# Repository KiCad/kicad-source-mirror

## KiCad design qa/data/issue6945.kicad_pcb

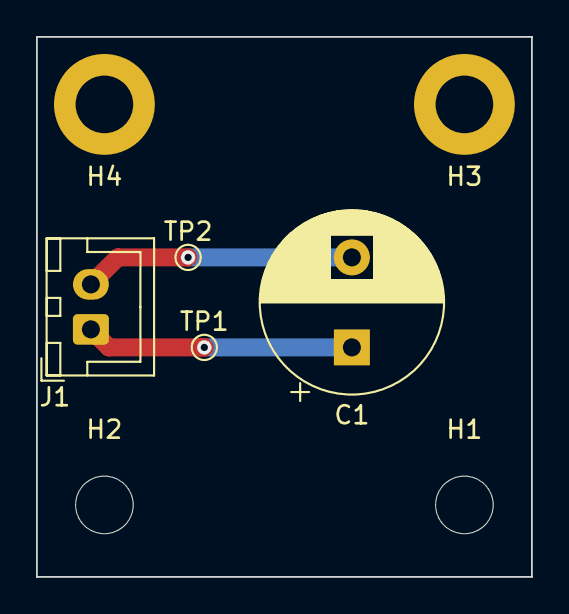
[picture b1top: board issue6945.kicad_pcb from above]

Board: 2 copper layers, 27.5 x 30.0 mm, 8 parts (0 on the bottom side), 2 nets.

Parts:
C1: 1m25vPY_5x10x16; CP_Radial_D10.0mm_P5.00mm
H1, H2: NPTH-3mm; MountingHole_3.2mm_M3
H3, H4: PTH-3mm; MountingHole_3.2mm_M3_DIN965_Pad
J1: XH-2A; JST_XH_B2B-XH-A_1x02_P2.50mm_Vertical
TP1, TP2: 1mm; TestPoint_Pad_D1.0mm

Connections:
GND: C1.2, J1.2, TP2.1
unnamed: C1.1, J1.1, TP1.1

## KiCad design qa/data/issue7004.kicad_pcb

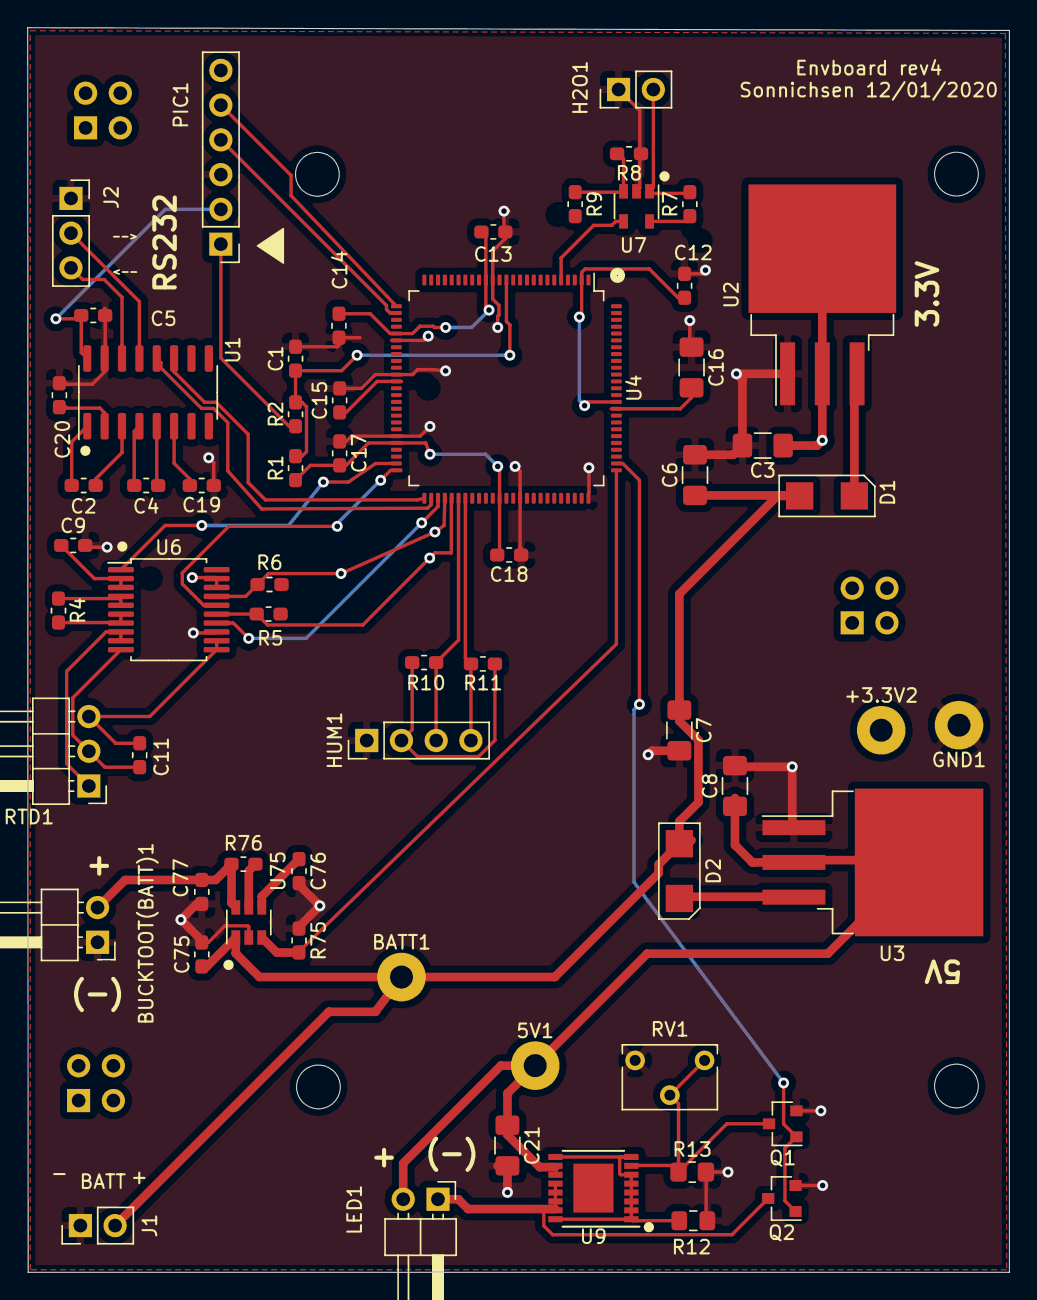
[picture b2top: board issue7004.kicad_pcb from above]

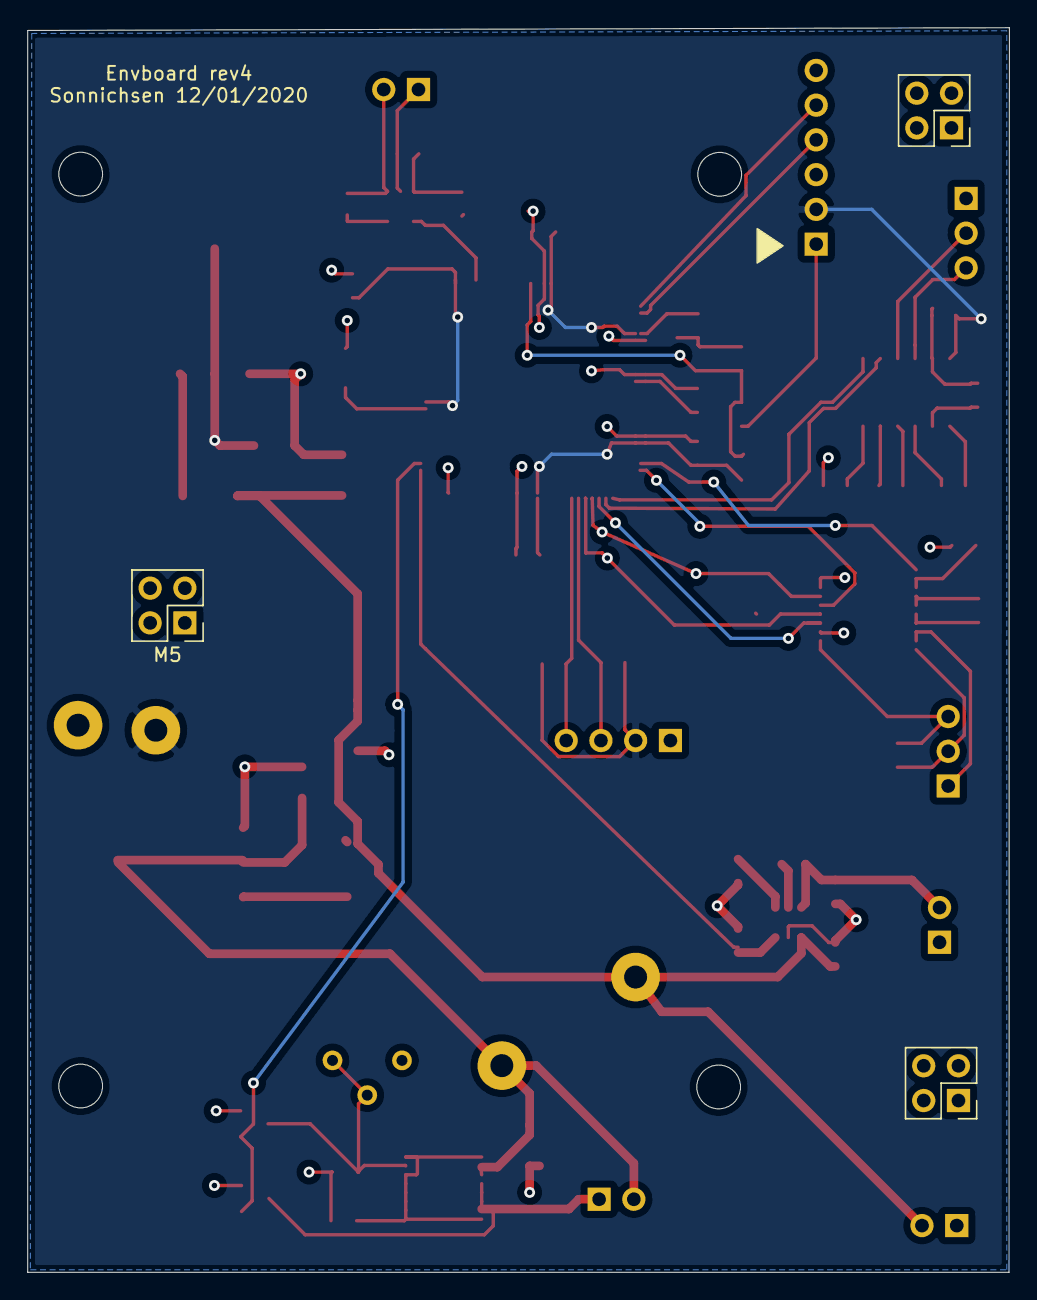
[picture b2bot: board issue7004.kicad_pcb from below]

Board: 2 copper layers, 71.8 x 91.0 mm, 69 parts (7 on the bottom side), 44 nets.

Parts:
5V1: TestPoint; post_small
+3.3V2: TestPoint; post_small
BATT1: TestPoint; post_small
BUCKTOOT(BATT)1: Conn_01x02; PinHeader_1x02_P2.54mm_Horizontal
C1, C2, C4, C5, C9, C11, C12, C13, C14, C15, C17, C18, C19, C20: 0.1uF; C_0603_1608Metric_Pad1.05x0.95mm_HandSolder
C3, C6, C7, C8, C16, C21: 10uF; C_1206_3216Metric_Pad1.42x1.75mm_HandSolder
C75: 1uF; R_0603_1608Metric_Pad1.05x0.95mm_HandSolder
C76: 0.01uF; R_0603_1608Metric_Pad1.05x0.95mm_HandSolder
C77: 0.1uF; R_0603_1608Metric_Pad1.05x0.95mm_HandSolder
D1, D2: MBRA130; 403D
GND1: TestPoint; post_small
H2O1: Conn_01x02; PinHeader_1x02_P2.54mm_Vertical
HUM1: SPARKSi7021; PinHeader_1x04_P2.54mm_Vertical
J1: Conn_01x02; PinHeader_1x02_P2.54mm_Vertical
J2: Conn_01x03; PinSocket_1x03_P2.54mm_Vertical
LED1: Conn_01x02; PinHeader_1x02_P2.54mm_Horizontal
M1, M2, M5: Conn_02x02_Odd_Even; PinHeader_2x02_P2.54mm_Vertical
PIC1: Conn_01x06; PinHeader_1x06_P2.54mm_Vertical
Q1, Q2: DMG3406L; SOT-23
R1, R5, R6, R10, R11, R75, R76: 10K; R_0603_1608Metric_Pad1.05x0.95mm_HandSolder
R2: 470; R_0603_1608Metric_Pad1.05x0.95mm_HandSolder
R4: 4K; R_0603_1608Metric_Pad1.05x0.95mm_HandSolder
R7: 1M; R_0603_1608Metric_Pad1.05x0.95mm_HandSolder
R8, R9: 100K; R_0603_1608Metric_Pad1.05x0.95mm_HandSolder
R12: 0.5ohms; R_0805_2012Metric_Pad1.15x1.40mm_HandSolder
R13: 15K; R_0805_2012Metric_Pad1.20x1.40mm_HandSolder
RTD1: Conn_01x03; PinHeader_1x03_P2.54mm_Horizontal
RV1: 50K; Potentiometer_Bourns_3266W_Vertical
U1: MAX3232CSE; SOIC-16_3.9x9.9mm_P1.27mm
U2: LM1084-3.3; TO-263-3_TabPin2
U3: LM1084-5.0; TO-263-3_TabPin2
U4: PIC24
U6: MAX31865xAP; MAX31865
U7: TL331; SOT-23-5
U9: LT3083; TSSOP-16-1EP_4.4x5mm_P0.65mm
U75: TPS22810; SOT-23-6
h1, h2, h3, h4: MountingHole_3.2mm_M3

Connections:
+3V3: +3.3V2.1, C3.1, C5.1, C9.1, C12.2, C13.2, C14.2, C15.2, C17.2, C18.2, HUM1.2, PIC1.2, R1.1, R5.2, R6.2, R7.1, R9.2, R10.2, R11.2, U1.16, U2.2, U4.2, U4.16, U4.30, U4.37, U4.46, U4.62, U4.86, U6.2, U6.3, U7.5
+5V: 5V1.1, C8.1, C21.1, LED1.2, U3.2, U9.10, U9.11
BATT: BATT1.1, C6.1, C7.1, C75.1, D1.2, D2.2, J1.2, U75.1
BUCK: R75.2, U4.76, U75.3
GND: BUCKTOOT(BATT)1.1, C1.2, C3.2, C5.2, C6.2, C7.2, C8.2, C9.2, C12.1, C13.1, C14.1, C15.1, C16.1, C17.1, C18.1, C19.1, C20.2, C21.2, C75.2, C76.2, C77.2, GND1.1, H2O1.1, HUM1.1, J1.1, J2.1, PIC1.3, Q1.2, Q2.2, R8.1, R12.2, R13.2, R75.1, RV1.3, U1.15, U2.1, U3.1, U4.15, U4.31, U4.36, U4.45, U4.65, U4.75, U6.13, U6.18, U6.19, U7.2, U75.2
H2O: U4.5, U7.4
LED: Q1.1, Q2.1, U4.77
MCLR: C1.1, R1.2, R2.2, U4.13
MISO: R6.1, U4.54, U6.17
MOSI: U4.53, U6.14
unnamed: BUCKTOOT(BATT)1.2, C77.1, R76.2, U75.6
unnamed: C2.1, U1.1
unnamed: C2.2, U1.3
unnamed: C4.1, U1.4
unnamed: C4.2, U1.5
unnamed: C11.1, RTD1.3, U6.11, U6.12
unnamed: C11.2, RTD1.2, U6.10
unnamed: C16.2, U4.85
unnamed: C19.2, U1.6
unnamed: C20.1, U1.2
unnamed: C76.1, U75.4
unnamed: D1.1, U2.3
unnamed: D2.1, U3.3
unnamed: H2O1.2, R7.2, U7.1
unnamed: J2.2, U1.13
unnamed: J2.3, U1.14
unnamed: LED1.1, Q2.3, U9.12, U9.13, U9.14, U9.15
unnamed: PIC1.1, R2.1
unnamed: Q1.3, R13.1, RV1.1, RV1.2, U9.7
unnamed: R4.1, U6.4, U6.5
unnamed: R4.2, U6.6, U6.7
unnamed: R8.2, R9.1, U7.3
unnamed: R12.1, U9.1, U9.2, U9.3, U9.4, U9.5, U9.6, U9.8, U9.9, U9.16
unnamed: R76.1, U75.5
unnamed: RTD1.1, U6.8, U6.9
PGC: PIC1.5, U4.26
PGD: PIC1.4, U4.27
PR5: U1.12, U4.52
PT5: U1.11, U4.51
SCK1: R5.1, U4.55, U6.15
SCL1: HUM1.4, R11.1, U4.57
SDA1: HUM1.3, R10.1, U4.56
\CS: U4.50, U6.16
\DRDY: U4.49, U6.1

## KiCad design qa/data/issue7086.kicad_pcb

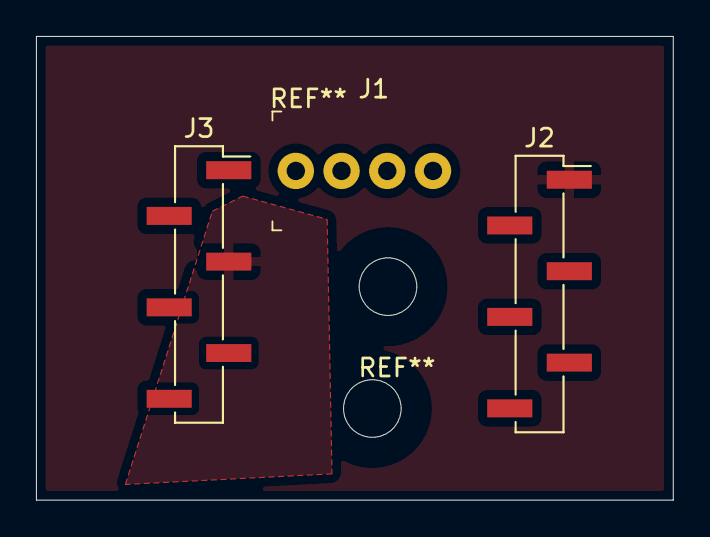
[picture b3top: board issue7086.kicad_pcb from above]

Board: 2 copper layers, 35.4 x 25.8 mm, 4 parts (0 on the bottom side), 2 nets, no tracks yet.

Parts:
H1: MountingHole; MountingHole_3.2mm_M3_DIN965
J1: 0022232041; PinHeader_1x4_P2.54mm_Drill1.02mm
J2, J3: 0022232041; PinHeader_1x06_P2.54mm_Vertical_SMD_Pin1Right

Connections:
unnamed: J1.2, J3.1
unnamed: J1.1, J1.4, J2.4, J3.4

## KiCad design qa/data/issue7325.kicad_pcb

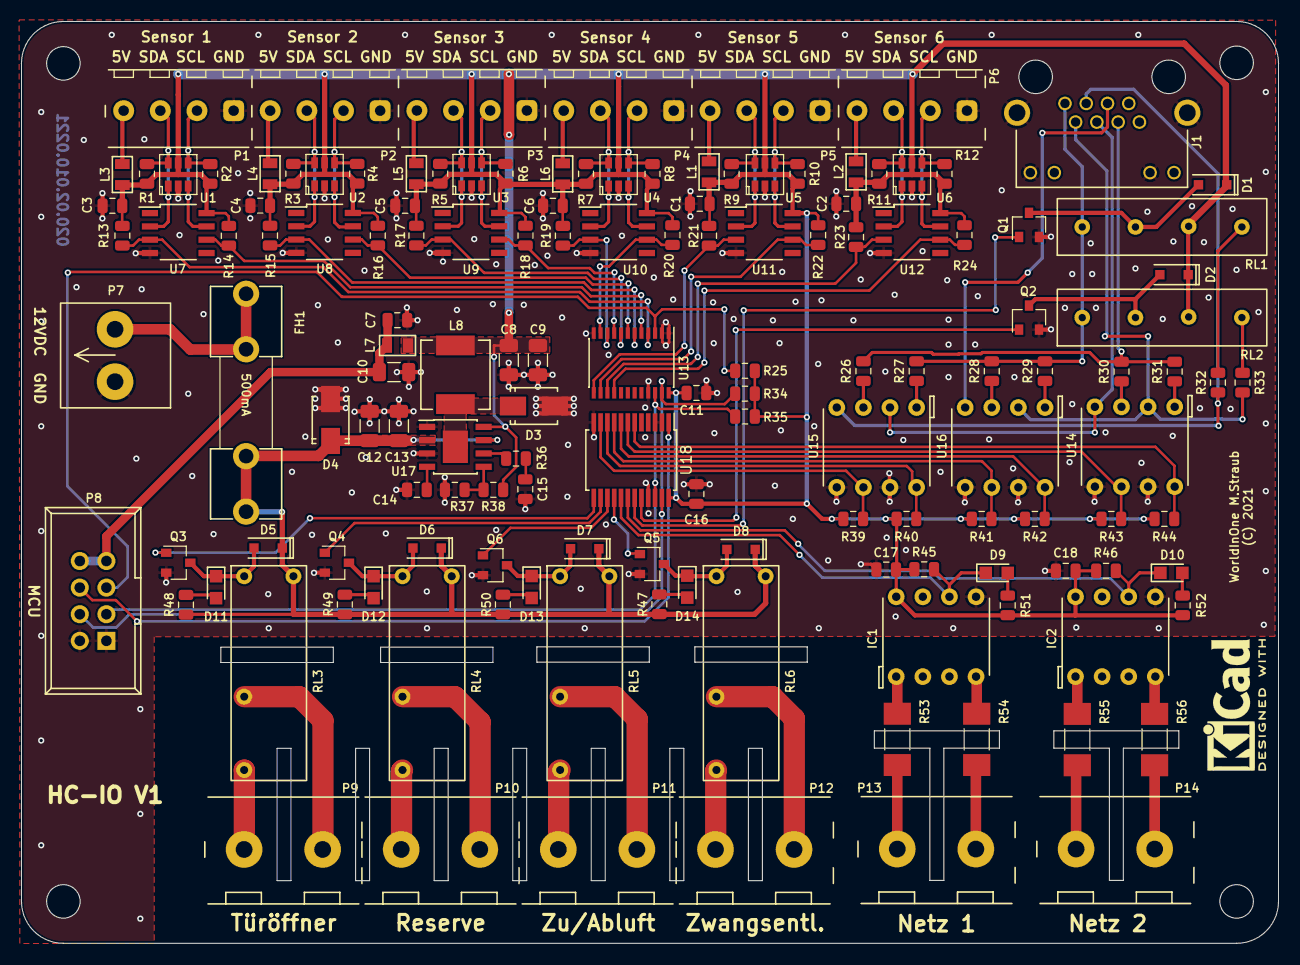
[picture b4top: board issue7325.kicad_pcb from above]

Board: 2 copper layers, 120.0 x 88.0 mm, 148 parts (0 on the bottom side), 100 nets.

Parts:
C1, C2, C3, C4, C5, C6: 1µ; C_0805_2012Metric_95
C7, C11, C14, C16, C17, C18: 100N; C_0805_2012Metric_60
C8, C9, C10, C12, C13: 22µ; C_1206_3216Metric_95
C15: 1.8N; C_0805_2012Metric_60
D1, D2, D5, D6, D7, D8: 1N4148WS; SOD-323
D3, D4: SS34; SMA_Standard
D9, D10: LED0805-Y; LED_0805
D11, D12, D13, D14: LED0805-G; LED_0805
FH1: FC5X20; Fuseholder5x20_horizontal_open_inline_1
IC1, IC2: HCPL-3760; DIP-8_W7.62mm_Socketed
J1: RJ45_LEDs_Shield
L1, L2, L3, L4, L5, L6, L7: FB; INDC2012X110
L8: 10µ; Inductor_0630
MH1, MH2, MH3, MH4: MHNP_M3; MountingHole_3.2mm_M3
P1, P2, P3, P4, P5, P6: KF128-4-3.5
P7: KF128-2-5.0
P8: IDCMV-4-2; IDC_Header_Straight_8pins
P9, P10, P11, P12, P13, P14: KF128-7.5-2; Terminal_Block_KF128_7.5mm-2pol
Q1, Q2, Q3, Q4, Q5, Q6: BSS138; SOT-23
R1, R2, R3, R4, R5, R6, R7, R8, R9, R10, R11, R12: 680E; R_0805_2012Metric
R13, R14, R15, R16, R17, R18, R19, R20, R21, R22, R23, R24, R25, R34, R35: 2.2K; R_0805_2012Metric
R26, R27, R28, R29, R30: 150E; R_0805_2012Metric
R31: 560E; R_0805_2012Metric
R32, R33: 10K; R_0805_2012Metric
R36: 27K; R_0805_2012Metric
R37: 9.53K; R_0805_2012Metric
R38: 49.9K; R_0805_2012Metric
R39, R40, R41, R42, R43, R44: 1K; R_0805_2012Metric
R45, R46, R51, R52: 4.7K; R_0805_2012Metric
R47, R48, R49, R50: 3.3K; R_0805_2012Metric
R53, R54, R55, R56: 82K; R_MELF_MMB-0207
RL1, RL2: SIP-1A5
RL3, RL4, RL5, RL6: G5NB-5; Relais_G5NB
U1, U2, U3, U4, U5, U6: USBLC6-2SC6; SOT-23-6
U7, U8, U9, U10, U11, U12: P82B715; SOIC-8_3.9x4.9mm_Pitch1.27mm
U13: PCA9548A; TSSOP-24_4.4x7.8mm_Pitch0.65mm
U14, U15, U16: LTV-827C; DIP-8_W7.62mm_Socketed
U17: AOZ3015; SOIC-8-1EP_3.9x4.9mm_Pitch1.27mm_PowerPAD
U18: PCF8575; SSOP-24_5.3x8.2mm_Pitch0.65mm

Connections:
/5V: C1.1, C2.1, C3.1, C4.1, C5.1, C6.1, C8.1, C9.1, C11.1, C16.2, C17.2, C18.2, D1.1 (K), D2.1 (K), IC1.8 (VCC), IC2.8 (VCC), L1.1, L2.1, L3.1, L4.1, L5.1, L6.1, L7.1, L8.2, R1.1, R2.2, R3.1, R4.2, R5.1, R6.2, R7.1, R8.2, R9.1, R10.2, R11.1, R12.2, R13.1, R14.1, R15.1, R16.1, R17.1, R18.1, R19.1, R20.1, R21.1, R22.1, R23.1, R24.1, R25.2, R34.1, R35.1, R38.2, R39.1, R40.1, R41.1, R42.1, R43.1, R44.1, R45.1, R46.1, R51.1, R52.1, RL1.3, RL2.3, U1.5 (VBUS), U2.5 (VBUS), U3.5 (VBUS), U4.5 (VBUS), U5.5 (VBUS), U6.5 (VBUS), U7.8 (Vcc), U8.8 (Vcc), U9.8 (Vcc), U10.8 (Vcc), U11.8 (Vcc), U12.8 (Vcc), U13.24 (VCC), U17.8 (VOUT), U18.24 (VDD)
/5VMCU: C7.1, C10.1, L7.2, P8.7, P8.8
/12V: C12.1, C13.1, D4.1 (K), D5.1 (K), D6.1 (K), D7.1 (K), D8.1 (K), FH1.2, R47.2, R48.2, R49.2, R50.2, RL3.4, RL4.4, RL5.4, RL6.4, U17.2 (VIN), U17.7 (EN)
/230V & general interface/230V1: D9.1 (K), IC1.6 (Vo), R45.2, U18.17 (IO1_4)
/230V & general interface/230V2: D10.1 (K), IC2.6 (Vo), R46.2, U18.18 (IO1_5)
/230V & general interface/AUX: Q4.1 (G), U18.14 (IO1_1)
/230V & general interface/BTL1: R42.2, U16.8, U18.8 (IO0_4)
/230V & general interface/BTL3: R40.2, U15.8, U18.10 (IO0_6)
/230V & general interface/BTL4: R41.2, U16.6, U18.9 (IO0_5)
/230V & general interface/BTL5: R44.2, U14.8, U18.6 (IO0_2)
/230V & general interface/BTL6: R39.2, U15.6, U18.11 (IO0_7)
/230V & general interface/BTL7: R43.2, U14.6, U18.7 (IO0_3)
/230V & general interface/BTP1: J1.1, R27.2, R28.2, R29.2, RL1.1, RL2.1
/230V & general interface/BTP2: J1.2, R33.2, U14.2, U16.2
/230V & general interface/BTP3: J1.3, R32.2, U15.4
/230V & general interface/BTP4: J1.4, U14.4, U15.2
/230V & general interface/BTP5: J1.5, U16.4
/230V & general interface/BTP6: J1.6, R26.2, R30.2, R31.2
/230V & general interface/DOOR: Q3.1 (G), U18.13 (IO1_0)
/230V & general interface/ENTFON: Q2.1 (G), U18.20 (IO1_7)
/230V & general interface/ENTFRH: Q1.1 (G), U18.19 (IO1_6)
/230V & general interface/ZUAB: Q6.1 (G), U18.15 (IO1_2)
/230V & general interface/ZWANG: Q5.1 (G), U18.16 (IO1_3)
/AM2315 sensors I2C interface/S0SCL: P1.2, R2.1, U1.3 (IO2), U1.4 (IO2), U7.7 (Ly)
/AM2315 sensors I2C interface/S0SDA: P1.3, R1.2, U1.1 (IO1), U1.6 (IO1), U7.2 (Lx)
/AM2315 sensors I2C interface/S1SCL: P2.2, R4.1, U2.3 (IO2), U2.4 (IO2), U8.7 (Ly)
/AM2315 sensors I2C interface/S1SDA: P2.3, R3.2, U2.1 (IO1), U2.6 (IO1), U8.2 (Lx)
/AM2315 sensors I2C interface/S2SCL: P3.2, R6.1, U3.3 (IO2), U3.4 (IO2), U9.7 (Ly)
/AM2315 sensors I2C interface/S2SDA: P3.3, R5.2, U3.1 (IO1), U3.6 (IO1), U9.2 (Lx)
/AM2315 sensors I2C interface/S3SCL: P4.2, R8.1, U4.3 (IO2), U4.4 (IO2), U10.7 (Ly)
/AM2315 sensors I2C interface/S3SDA: P4.3, R7.2, U4.1 (IO1), U4.6 (IO1), U10.2 (Lx)
/AM2315 sensors I2C interface/S4SCL: P5.2, R10.1, U5.3 (IO2), U5.4 (IO2), U11.7 (Ly)
/AM2315 sensors I2C interface/S4SDA: P5.3, R9.2, U5.1 (IO1), U5.6 (IO1), U11.2 (Lx)
/AM2315 sensors I2C interface/S5SCL: P6.2, R12.1, U6.3 (IO2), U6.4 (IO2), U12.7 (Ly)
/AM2315 sensors I2C interface/S5SDA: P6.3, R11.2, U6.1 (IO1), U6.6 (IO1), U12.2 (Lx)
/NIOINT: P8.6, U18.1 (~INT)
/NIORESET: P8.5, R25.1, U13.3 (~RESET)
/SCL: P8.3, R35.2, U13.22 (SCL), U18.22 (SCL)
/SDA: P8.4, R34.2, U13.23 (SDA), U18.23 (SDA)
GND: C1.2, C2.2, C3.2, C4.2, C5.2, C6.2, C7.2, C8.2, C9.2, C10.2, C11.2, C12.2, C13.2, C14.2, C15.2, C16.1, C17.1, C18.1, D3.2 (A), D4.2 (A), IC1.5 (GND), IC2.5 (GND), J1.GK, J1.Shld (Shield), J1.YK, P1.1, P2.1, P3.1, P4.1, P5.1, P6.1, P7.1, P8.1, P8.2, Q1.2 (S), Q2.2 (S), Q3.2 (S), Q4.2 (S), Q5.2 (S), Q6.2 (S), R37.1, U1.2 (GND), U2.2 (GND), U3.2 (GND), U4.2 (GND), U5.2 (GND), U6.2 (GND), U7.4 (GND), U8.4 (GND), U9.4 (GND), U10.4 (GND), U11.4 (GND), U12.4 (GND), U13.1 (A0), U13.2 (A1), U13.12 (GND), U13.21 (A2), U14.5, U14.7, U15.5, U15.7, U16.5, U16.7, U17.1 (PGND), U17.3 (AGND), U18.2 (A1), U18.3 (A2), U18.12 (VSS), U18.21 (A0)
unnamed: C14.1, U17.4 (VCC)
unnamed: C15.1, R36.1
unnamed: D1.2 (A), Q1.3 (D), RL1.2
unnamed: D2.2 (A), Q2.3 (D), RL2.2
unnamed: D3.1 (K), L8.1, U17.9 (LX)
unnamed: D9.2 (A), R51.2
unnamed: D10.2 (A), R52.2
unnamed: D5.2 (A), D11.1 (K), Q3.3 (D), RL3.1
unnamed: D11.2 (A), R48.1
unnamed: D6.2 (A), D12.1 (K), Q4.3 (D), RL4.1
unnamed: D12.2 (A), R49.1
unnamed: D7.2 (A), D13.1 (K), Q6.3 (D), RL5.1
unnamed: D13.2 (A), R50.1
unnamed: D8.2 (A), D14.1 (K), Q5.3 (D), RL6.1
unnamed: D14.2 (A), R47.1
unnamed: FH1.1, P7.2
unnamed: IC1.1 (AC+), R53.1
unnamed: IC1.4 (AC-), R54.1
unnamed: IC2.1 (AC+), R55.1
unnamed: IC2.4 (AC-), R56.1
unnamed: L1.2, P5.4
unnamed: L2.2, P6.4
unnamed: L3.2, P1.4
unnamed: L4.2, P2.4
unnamed: L5.2, P3.4
unnamed: L6.2, P4.4
unnamed: P9.1, RL3.2
unnamed: P9.2, RL3.3
unnamed: P10.1, RL4.2
unnamed: P10.2, RL4.3
unnamed: P11.1, RL5.2
unnamed: P11.2, RL5.3
unnamed: P12.1, RL6.2
unnamed: P12.2, RL6.3
unnamed: P13.1, R54.2
unnamed: P13.2, R53.2
unnamed: P14.1, R56.2
unnamed: P14.2, R55.2
unnamed: R13.2, U7.3 (Sx), U13.4 (SD0)
unnamed: R14.2, U7.6 (Sy), U13.5 (SC0)
unnamed: R15.2, U8.3 (Sx), U13.6 (SD1)
unnamed: R16.2, U8.6 (Sy), U13.7 (SC1)
unnamed: R17.2, U9.3 (Sx), U13.8 (SD2)
unnamed: R18.2, U9.6 (Sy), U13.9 (SC2)
unnamed: R19.2, U10.3 (Sx), U13.10 (SD3)
unnamed: R20.2, U10.6 (Sy), U13.11 (SC3)
unnamed: R21.2, U11.3 (Sx), U13.13 (SD4)
unnamed: R22.2, U11.6 (Sy), U13.14 (SC4)
unnamed: R23.2, U12.3 (Sx), U13.15 (SD5)
unnamed: R24.2, U12.6 (Sy), U13.16 (SC5)
unnamed: R26.1, U15.3
unnamed: R27.1, U15.1
unnamed: R28.1, U16.3
unnamed: R29.1, U16.1
unnamed: R30.1, U14.3
unnamed: R31.1, U14.1
unnamed: R32.1, RL1.4
unnamed: R33.1, RL2.4
unnamed: R36.2, U17.6 (CMP)
unnamed: R37.2, R38.1, U17.5 (FB)

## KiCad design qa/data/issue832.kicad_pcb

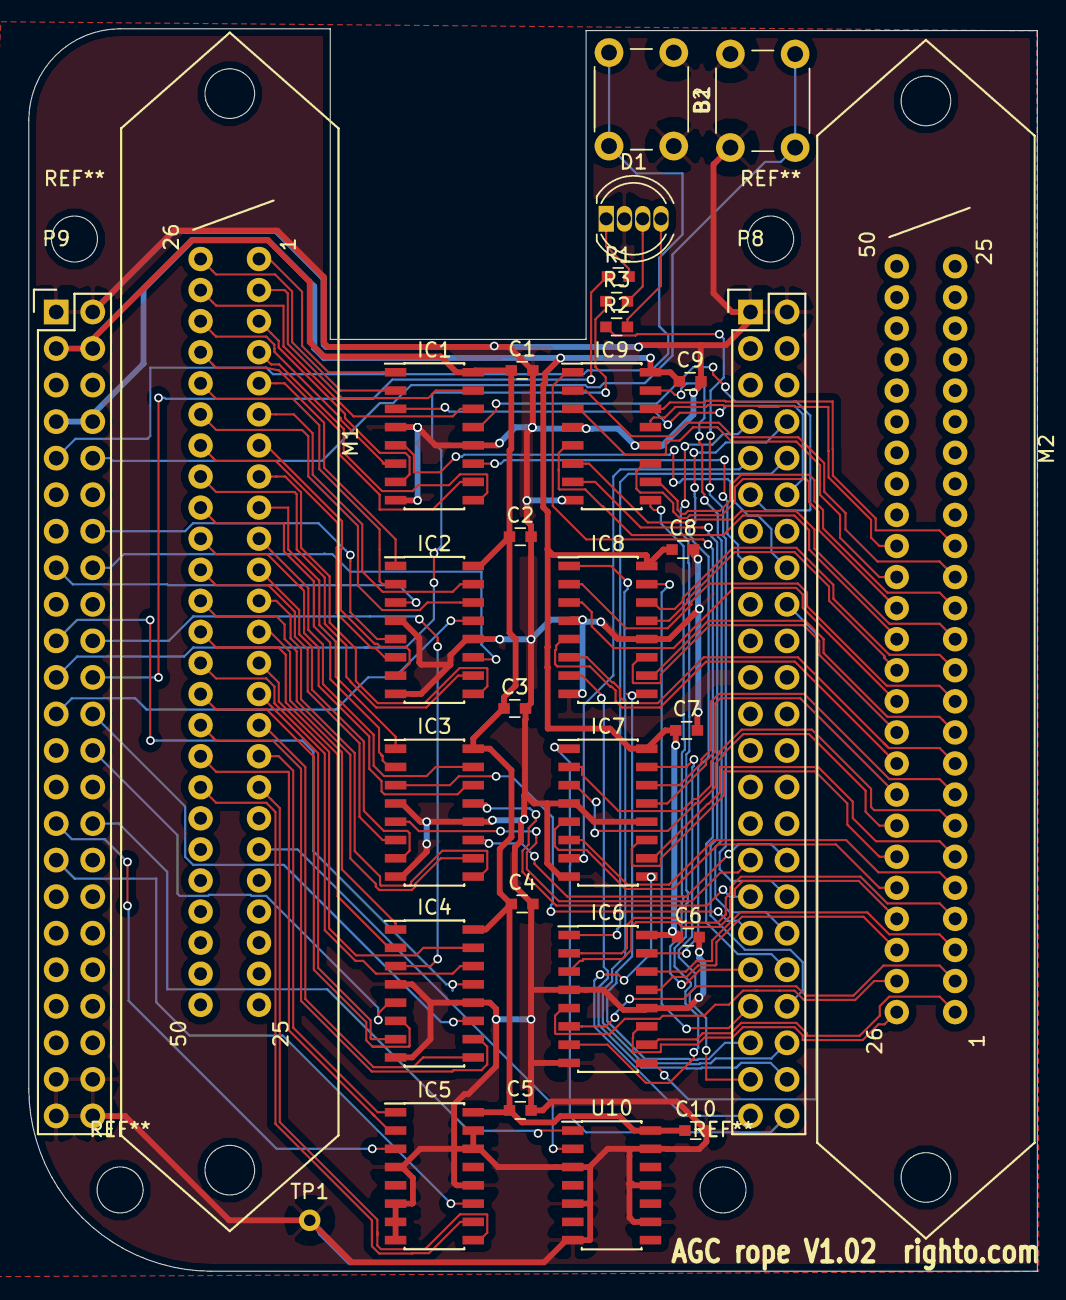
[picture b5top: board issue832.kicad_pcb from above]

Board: 2 copper layers, 70.1 x 86.4 mm, 31 parts (0 on the bottom side), 115 nets.

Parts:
B1, B2: SW_Push; SW_PUSH_6mm
C1, C2, C3, C4, C5, C6, C7, C8, C9, C10: .1UF; C_0603
D1: LED_RCGB; LED_D5.0mm-4
IC1, IC2, IC3, IC4, IC5: AM26C32; SOIC-16_3.9x9.9mm_Pitch1.27mm
IC6, IC7, IC8, IC9: AM26C31; SOIC-16_3.9x9.9mm_Pitch1.27mm
M1: 50-PIN-CENTRONICS-FFEMALE; CENTRONICS-50-F
M2: 50-PIN-CENTRONICS-MMALE; CENTRONICS-50-M
P8, P9: BeagleBone_Black_Header; Socket_BeagleBone_Black
R1, R2, R3: 220; C_0603
TP1: TestPoint; Measurement_Point_Round-TH_Small
U10: 74LVC07; SOIC-14_3.9x8.7mm_Pitch1.27mm

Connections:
+3V3: C1.1, C2.1, C3.1, C4.1, C5.1, C10.1, IC1.16, IC2.16, IC3.16, IC4.16, IC5.16, P9.3, P9.4, U10.14
/IL1: IC1.3, P8.12
/IL1+: IC1.2, M1.26
/IL1-: IC1.1, M1.1
/IL2: IC1.13, P8.11
/IL2+: IC1.14, M1.27
/IL2-: IC1.15, M1.2
/IL3: IC1.5, P8.16
/IL3+: IC1.6, M1.28
/IL3-: IC1.7, M1.3
/IL4: IC1.11, P8.15
/IL4+: IC1.10, M1.29
/IL4-: IC1.9, M1.4
/IL5: IC2.3, P9.15
/IL5+: IC2.2, M1.30
/IL5-: IC2.1, M1.5
/IL6: IC2.13, P9.23
/IL6+: IC2.14, M1.31
/IL6-: IC2.15, M1.6
/IL7: IC2.5, P9.14
/IL7+: IC2.6, M1.32
/IL7-: IC2.7, M1.7
/addr_okay: IC5.11, P9.31
/addr_okay+: IC5.10, M1.43
/addr_okay-: IC5.9, M1.18
/b: P8.34, R2.1
/clear: IC5.3, P9.29
/clear+: IC5.2, M1.42
/clear-: IC5.1, M1.17
/g: P9.21, R3.1
/plane0: IC2.11, P9.16
/plane0+: IC2.10, M1.33
/plane0-: IC2.9, M1.8
/plane1: IC3.3, P8.35
/plane1+: IC3.2, M1.34
/plane1-: IC3.1, M1.9
/plane2: IC3.13, P8.33
/plane2+: IC3.14, M1.35
/plane2-: IC3.15, M1.10
/plane3: IC3.5, P8.31
/plane3+: IC3.6, M1.36
/plane3-: IC3.7, M1.11
/plane4: IC3.11, P8.32
/plane4+: IC3.10, M1.37
/plane4-: IC3.9, M1.12
/plane5: IC4.3, P9.20
/plane5+: IC4.2, M1.38
/plane5-: IC4.1, M1.13
/plane6: IC4.13, P9.19
/plane6+: IC4.14, M1.39
/plane6-: IC4.15, M1.14
/plane7: IC4.5, P9.26
/plane7+: IC4.6, M1.40
/plane7-: IC4.7, M1.15
/plane8: IC4.11, P9.24
/plane8+: IC4.10, M1.41
/plane8-: IC4.9, M1.16
/r: P9.22, R1.1
/red: P9.30, U10.1
/red_out: M1.20, U10.2
/sense1: IC6.9, P8.18
/sense1+: IC6.10, M2.1
/sense1-: IC6.11, M2.26
/sense2: IC6.7, P8.7
/sense2+: IC6.6, M2.2
/sense2-: IC6.5, M2.27
/sense3: IC6.15, P8.8
/sense3+: IC6.14, M2.3
/sense3-: IC6.13, M2.28
/sense4: IC6.1, P8.10
/sense4+: IC6.2, M2.4
/sense4-: IC6.3, M2.29
/sense5: IC7.7, P8.9
/sense5+: IC7.6, M2.5
/sense5-: IC7.5, M2.30
/sense6: IC7.9, P8.45
/sense6+: IC7.10, M2.6
/sense6-: IC7.11, M2.31
/sense7: IC7.1, P8.46
/sense7+: IC7.2, M2.7
/sense7-: IC7.3, M2.32
/sense8: IC7.15, P8.43
/sense8+: IC7.14, M2.8
/sense8-: IC7.13, M2.33
/sense9: IC8.7, P8.44
/sense9+: IC8.6, M2.9
/sense9-: IC8.5, M2.34
/sense10: IC8.9, P8.41
/sense10+: IC8.10, M2.10
/sense10-: IC8.11, M2.35
/sense11: IC8.1, P8.42
/sense11+: IC8.2, M2.11
/sense11-: IC8.3, M2.36
/sense12: IC8.15, P8.39
/sense12+: IC8.14, M2.12
/sense12-: IC8.13, M2.37
/sense13: IC9.7, P8.40
/sense13+: IC9.6, M2.13
/sense13-: IC9.5, M2.38
/sense14: IC9.9, P8.37
/sense14+: IC9.10, M2.14
/sense14-: IC9.11, M2.39
/sense15: IC9.1, P8.38
/sense15+: IC9.2, M2.15
/sense15-: IC9.3, M2.40
/sense16: IC9.15, P8.36
/sense16+: IC9.14, M2.16
/sense16-: IC9.13, M2.41
GNDD: B1.1, B2.1, C1.2, C2.2, C3.2, C4.2, C5.2, C6.2, C7.2, C8.2, C9.2, C10.2, D1.2, IC1.4, IC1.8, IC1.12, IC2.4, IC2.8, IC2.12, IC3.4, IC3.8, IC3.12, IC4.4, IC4.8, IC4.12, IC5.4, IC5.6, IC5.7, IC5.8, IC5.12, IC5.14, IC5.15, IC6.4, IC6.8, IC6.12, IC7.4, IC7.8, IC7.12, IC8.4, IC8.8, IC8.12, IC9.4, IC9.8, IC9.12, P8.1, P8.2, P9.1, P9.2, P9.43, P9.44, P9.45, P9.46, TP1.1, U10.3, U10.5, U10.7, U10.9, U10.11, U10.13
unnamed: D1.1, R1.2
unnamed: D1.3, R3.2
unnamed: D1.4, R2.2
PWR_BUT: B1.2, P9.9
SYS_5V: C6.1, C7.1, C8.1, C9.1, IC6.16, IC7.16, IC8.16, IC9.16, P9.7, P9.8
SYS_RESETN: B2.2, P9.10

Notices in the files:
qa/data/issue7325.kicad_pcb:
(C) 2021
